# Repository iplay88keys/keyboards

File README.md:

# Keyboards

## Setup

`git submodule update --init --recursive`

To build on Ubuntu, these libraries are necessary:

  * gcc-avr
  * avr-libc
  * dfu-programmer
  * dfu-util (required for flashing)
  * make

And these may be necessary:

  * gcc-arm-none-eabi
   
(Successfully built on pocket chip)

## Some useful sites/tutorials

[tmk_firmware](https://github.com/tmk/tmk_keyboard)

[Keyboard Layout Editor](http://www.keyboard-layout-editor.com/)

[Plate and Case Builder](http://builder.swillkb.com/)

[KiCAD Keyboard PCB Design Guide](https://deskthority.net/wiki/KiCAD_keyboard_PCB_design_guide)

[BrownFox Step by Step](https://deskthority.net/workshop-f7/brownfox-step-by-step-t6050.html)

[How to Build Your Very Own Keyboard Firmware](https://deskthority.net/workshop-f7/how-to-build-your-very-own-keyboard-firmware-t7177.html)

## Acknowledgements

[tmk_keyboard](https://github.com/tmk/tmk_keyboard)

[ChibiOS](https://github.com/ChibiOS/ChibiOS)

[ChibiOS-Contrib](https://github.com/ChibiOS/ChibiOS-Contrib)

[njbair](https://github.com/njbair/keyboard_firmware)

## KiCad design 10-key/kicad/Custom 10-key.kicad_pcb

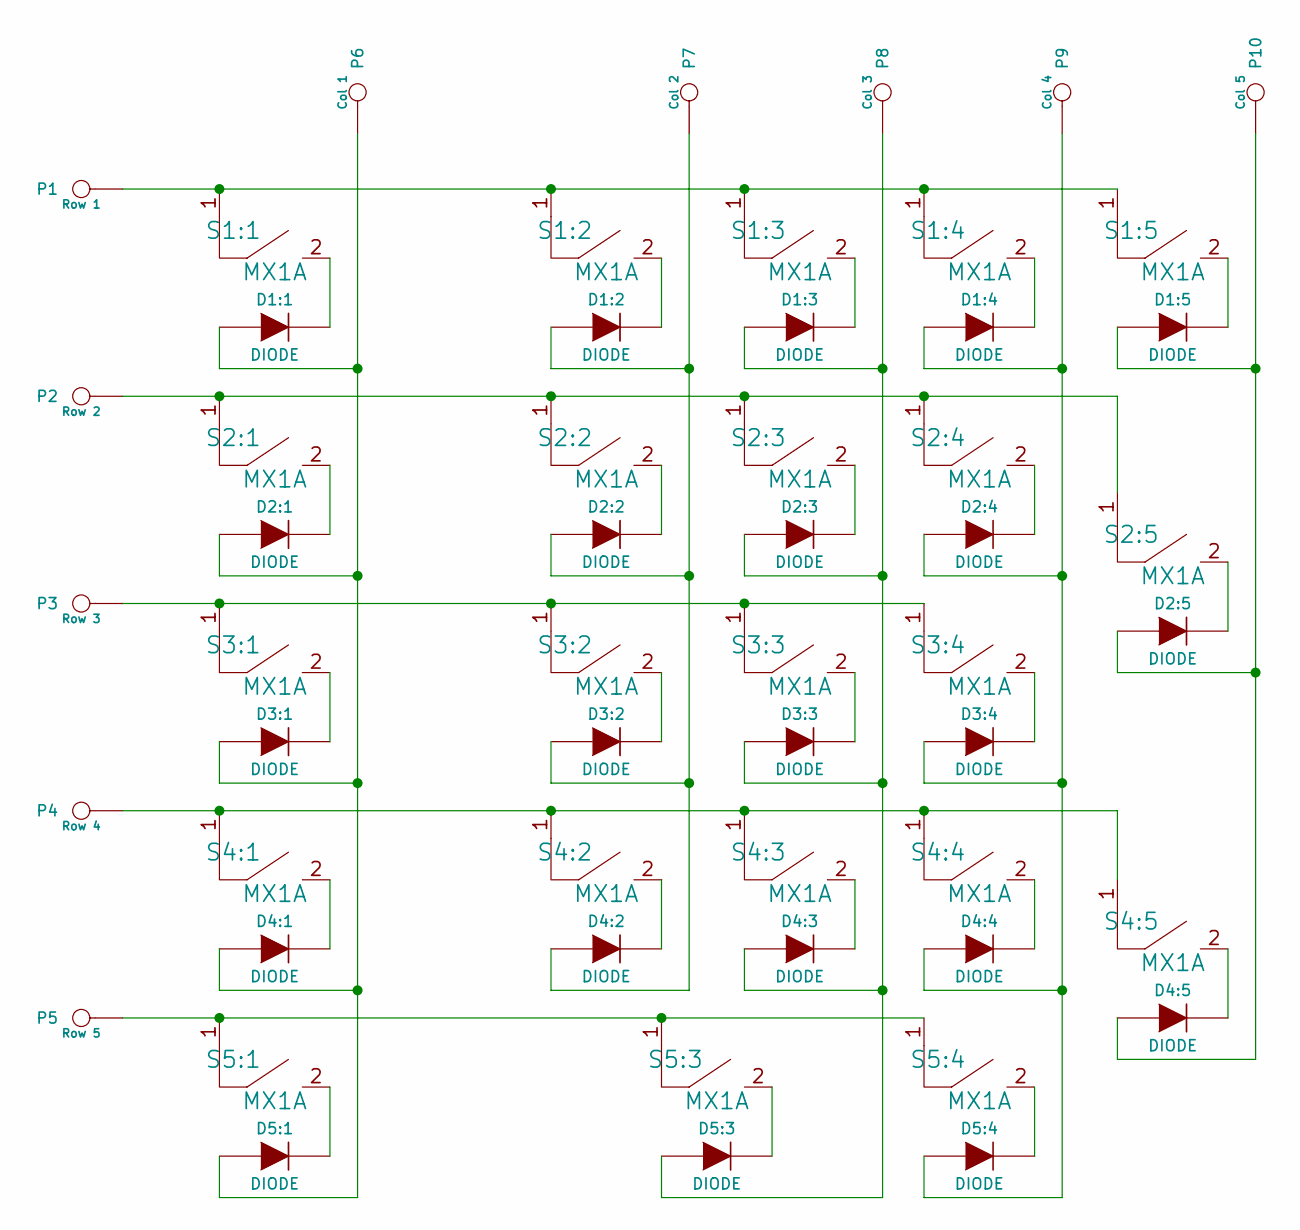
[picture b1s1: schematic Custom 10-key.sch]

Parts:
D1:1, D1:2, D1:3, D1:4, D1:5, D2:1, D2:2, D2:3, D2:4, D2:5, D3:1, D3:2, D3:3, D3:4, D4:1, D4:2, D4:3, D4:4, D4:5, D5:1, D5:3, D5:4: DIODE; SOD-123(A-C)
P1: Row 1; Pad
P2: Row 2; Pad
P3: Row 3; Pad
P4: Row 4; Pad
P5: Row 5; Pad
P6: Col 1; Pad
P7: Col 2; Pad
P8: Col 3; Pad
P9: Col 4; Pad
P10: Col 5; Pad
S1:1, S1:2, S1:3, S1:4, S1:5, S2:1, S2:2, S2:3, S2:4, S2:5, S3:1, S3:2, S3:3, S3:4, S4:1, S4:2, S4:3, S4:4, S4:5, S5:1, S5:3, S5:4: MX1A; CHERRY_PCB_100H_Plated

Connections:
unnamed: D1:1.A, D2:1.A, D3:1.A, D4:1.A, D5:1.A, P6.1
unnamed: D1:1.C (K), S1:1.2
unnamed: D1:2.A, D2:2.A, D3:2.A, D4:2.A, P7.1
unnamed: D1:2.C (K), S1:2.2
unnamed: D1:3.A, D2:3.A, D3:3.A, D4:3.A, D5:3.A, P8.1
unnamed: D1:3.C (K), S1:3.2
unnamed: D1:4.A, D2:4.A, D3:4.A, D4:4.A, D5:4.A, P9.1
unnamed: D1:4.C (K), S1:4.2
unnamed: D1:5.A, D2:5.A, D4:5.A, P10.1
unnamed: D1:5.C (K), S1:5.2
unnamed: D2:1.C (K), S2:1.2
unnamed: D2:2.C (K), S2:2.2
unnamed: D2:3.C (K), S2:3.2
unnamed: D2:4.C (K), S2:4.2
unnamed: D2:5.C (K), S2:5.2
unnamed: D3:1.C (K), S3:1.2
unnamed: D3:2.C (K), S3:2.2
unnamed: D3:3.C (K), S3:3.2
unnamed: D3:4.C (K), S3:4.2
unnamed: D4:1.C (K), S4:1.2
unnamed: D4:2.C (K), S4:2.2
unnamed: D4:3.C (K), S4:3.2
unnamed: D4:4.C (K), S4:4.2
unnamed: D4:5.C (K), S4:5.2
unnamed: D5:1.C (K), S5:1.2
unnamed: D5:3.C (K), S5:3.2
unnamed: D5:4.C (K), S5:4.2
unnamed: P1.1, S1:1.1, S1:2.1, S1:3.1, S1:4.1, S1:5.1
unnamed: P2.1, S2:1.1, S2:2.1, S2:3.1, S2:4.1, S2:5.1
unnamed: P3.1, S3:1.1, S3:2.1, S3:3.1, S3:4.1
unnamed: P4.1, S4:1.1, S4:2.1, S4:3.1, S4:4.1, S4:5.1
unnamed: P5.1, S5:1.1, S5:3.1, S5:4.1

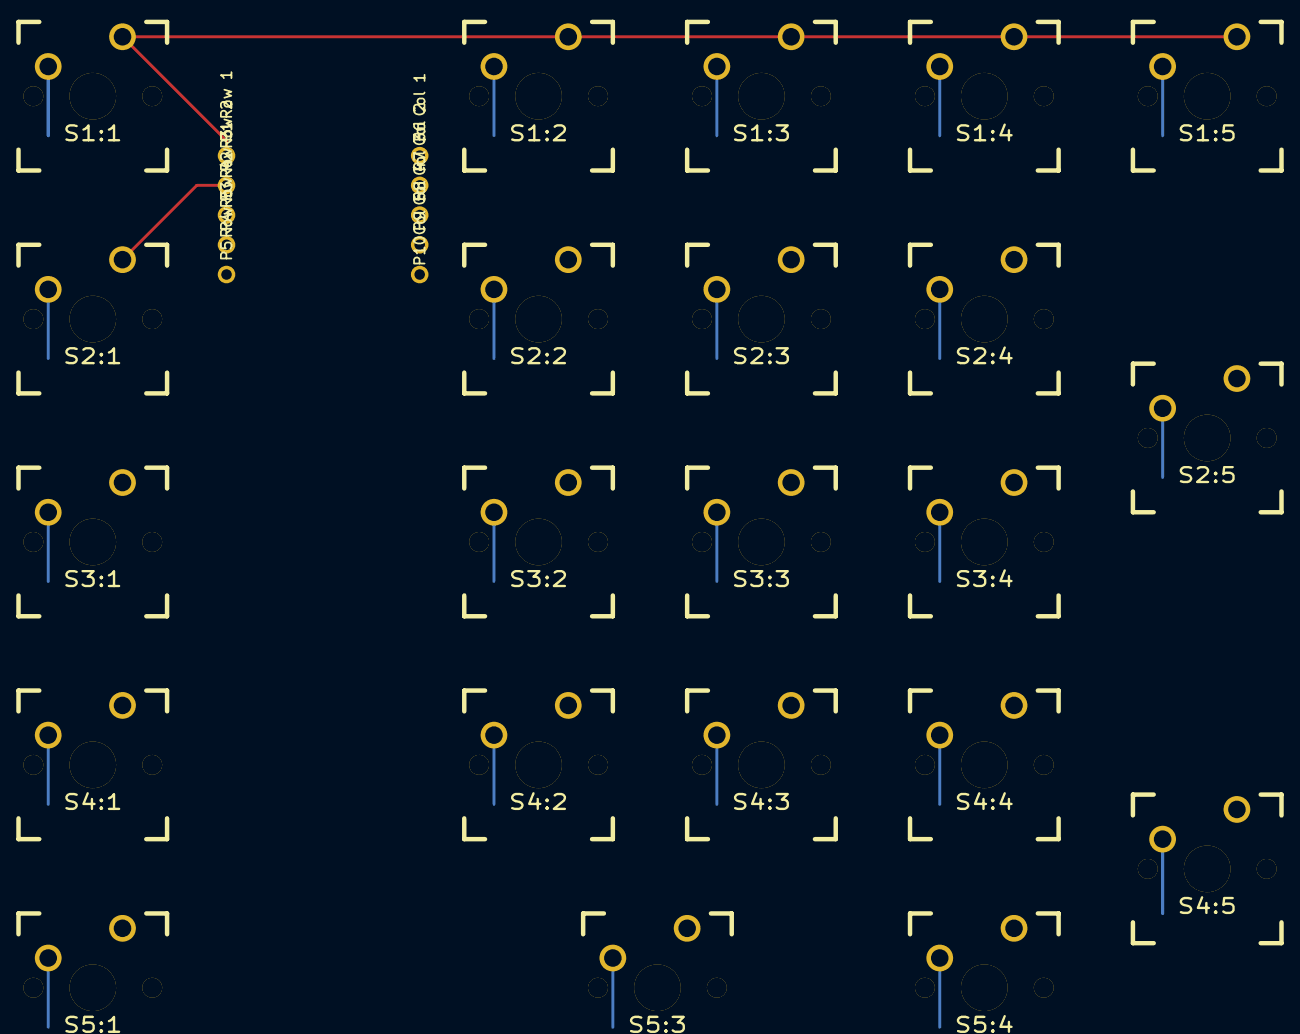
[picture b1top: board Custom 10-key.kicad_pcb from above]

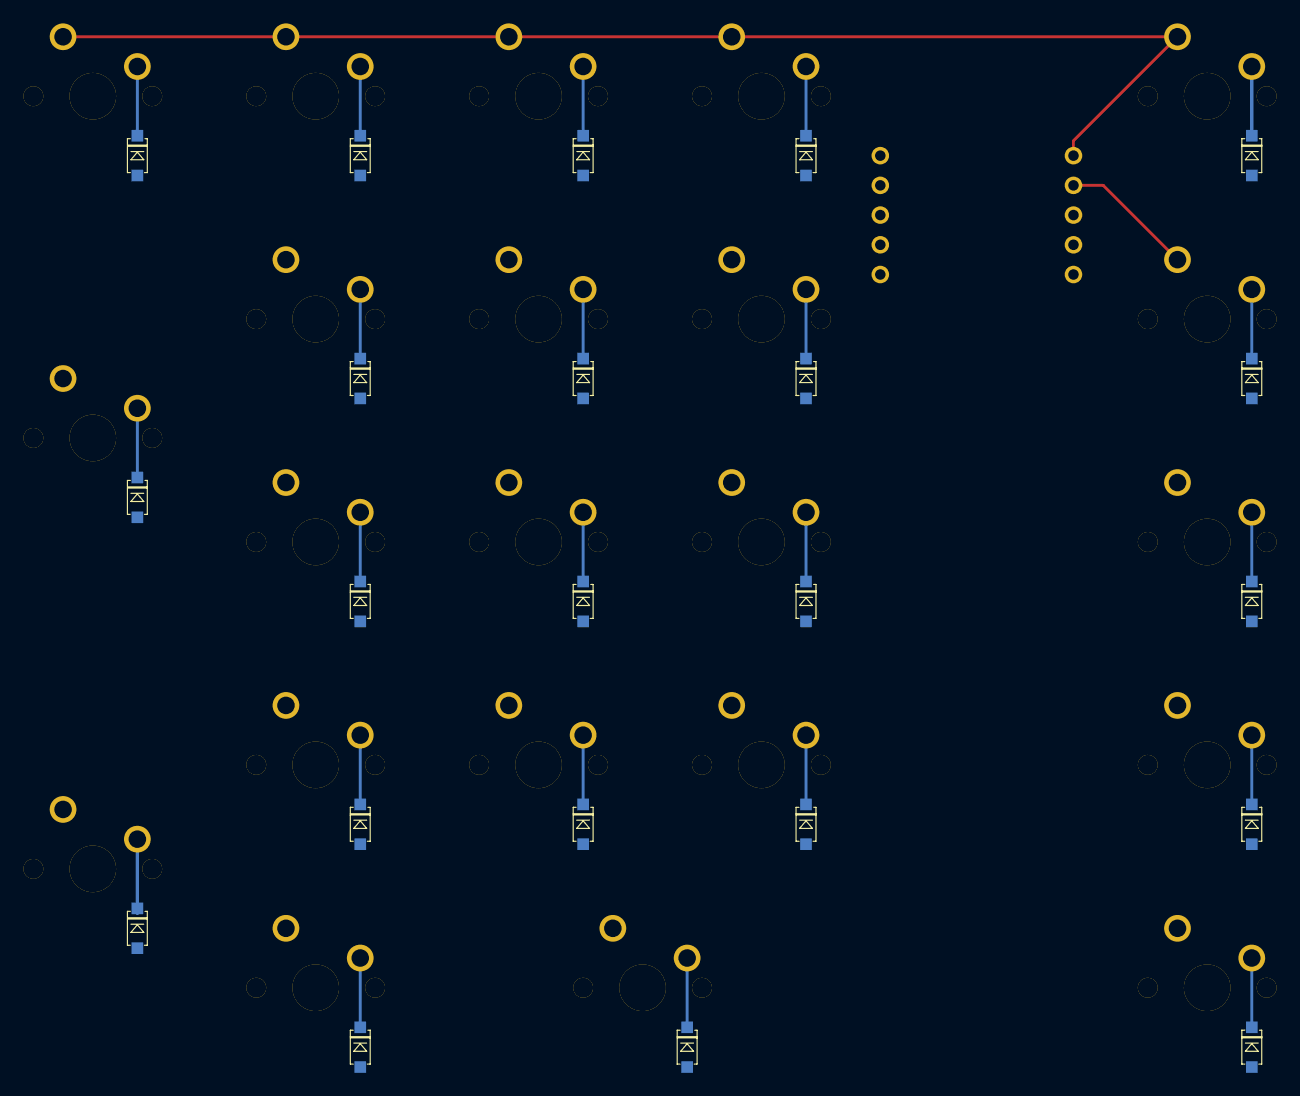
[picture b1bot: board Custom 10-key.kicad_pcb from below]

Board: 2 copper layers, 54 parts (22 on the bottom side), 32 nets.

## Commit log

2016-10-31 Add Gitter badge
2016-11-01 Add 10-key files and helpful links
2016-11-01 Update readme format
2016-11-01 Add 10-key kicad and layout files
2016-11-01 Update repo to be more self-contained
2016-11-01 Add tenkey images
2016-11-01 Update macros for tenkey
2016-12-25 Add initial whitefox configuration
2016-12-25 Update whitefox README with correct building steps
2017-03-12 Add ergodox layout files
2022-11-08 Add ergodox configuration
2022-11-16 Remove flash from first ergodox layers
2024-06-22 Updates for ergodox layout
